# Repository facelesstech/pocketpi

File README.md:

# pocketpi
raspberry pi zero w pocket terminal

Blog post - https://wp.me/pKY3w-qk
Youtube - https://www.youtube.com/watch?v=DJa4tzv_eco

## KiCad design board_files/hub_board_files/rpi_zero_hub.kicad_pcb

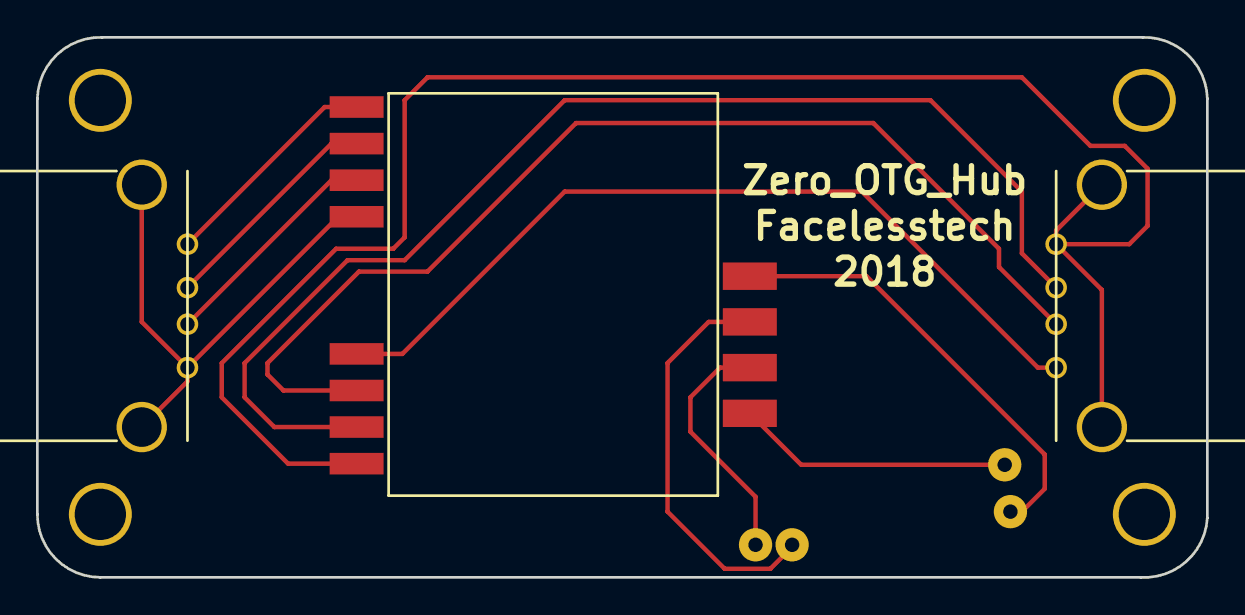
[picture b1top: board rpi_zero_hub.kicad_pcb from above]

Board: 2 copper layers, 65.0 x 30.0 mm, 4 parts (0 on the bottom side), 12 nets.

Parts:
P1: USB_A; raspberry_pi_zero_otg
P2, P3: USB_A; female_usb_custom
U1: USB_hub_custom; OTG_hub_custom

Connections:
unnamed: P1.1, U1.1
unnamed: P1.2, U1.2
unnamed: P1.3, U1.3
unnamed: P1.4, U1.4
unnamed: P2.1, U1.9
unnamed: P2.2, U1.10
unnamed: P2.3, U1.11
unnamed: P2.4, U1.12
unnamed: P3.1, U1.5
unnamed: P3.2, U1.6
unnamed: P3.3, U1.7
unnamed: P3.4, U1.8

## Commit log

2018-09-08 board files
2018-09-08 updated files
2018-09-12 added links
